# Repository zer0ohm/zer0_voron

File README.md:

# zer0_voron
## About zer0_voron
A repository for compiling modified parts, or a [hashtag](https://twitter.com/search?q=%23zer0_voron) to be added to tweets about VORON.

## BOM
Under development: It is a modification of an existing component, but it has never been tested and is "very" experimental. (To be tested soon, but undecided.)
### Shoiko(背負子)
 * Rear mounting of electrical components mod for VORON2.4
 * din_rail_mount_a/b inspired from [SnakeOil-XY](https://github.com/SnakeOilXY/SnakeOil-XY/blob/master/BETA2_Release/STLs/Panels/Back-panel/Bottom/4x_din-holder.stl)
 
| Part | Qty | Sourcing | Description/Note |
|---------|-------|----------------| ------------------ |
| din_rail_mount_x2 | 2 | Print part([STEP](./CAD/din_rail_mount_x2.step) or [STL](./STLs/din_rail_mount_x2.stl)) |  |
| SHCS M3x** | 2 | Local store | Length are TBD. |
| M3 Roll-in T-Nut | 2 | [AliExpress](https://www.aliexpress.com/item/32805163712.html) |  |
| SB2040 Cable-harness <br> or <br> 2-wire 18AWG Robot Cable(3 meter) + 2-wire AWG22 Robot Cable(3 meter) | 1 | [AliExpress](https://www.aliexpress.com/item/1005004819126687.html) <br> or <br> [Misumi(AWG18)](https://jp.misumi-ec.com/vona2/detail/222000262826/?HissuCode=%EF%BE%9B%EF%BE%8E%EF%BE%9E%EF%BE%84%EF%BD%AF%EF%BE%8C%EF%BE%9FDPC3+AWG18X2C-3) + <br> [Misumi(AWG22)](https://jp.misumi-ec.com/vona2/detail/222000262826/?HissuCode=%EF%BE%9B%EF%BE%8E%EF%BE%9E%EF%BE%84%EF%BD%AF%EF%BE%8C%EF%BE%9FDPC3+AWG22X2C-3)| Length are TBD. See [Cable Processing](./Docs/cable_processing.md) |
| RJ11 Cable | 1 | [Misumi](https://jp.misumi-ec.com/vona2/detail/110500076440/?HissuCode=CBLRJ050-666-S-07-SV) | For BTT Octopus only. See [Cable Processing](./Docs/cable_processing.md) |
| Toolhead PCB | 1 | [AliExpress](https://www.aliexpress.com/item/1005004675264551.html) | AliExpress's link is example for in Stealthburner. |
| BHCS M5x10 | 2 | Stock or Local store | Replace of screws due to removal of "XY Cable Chain Bridge". |

### Modified Corner Brackets
 * Attempt to determine if printed brackets can be used to strengthen rigidity
 * model based Misumi's HBLFSN5(2mm narrower to avoid interference with Z_Idler)

| Part | Qty | Sourcing | Description/Note |
|---------|-------|----------------| ------------------ |
| 2020Frame Corner Bracket 18mmWide | 12 | Print part([STEP](./CAD/2020_CornerBracket_18mm_x12.step) or [STL](./STLs/2020_CornerBracket_18mm_x12.stl)) ||
| SHCS M5x10 | 24 | Local store |  |
| M5 Roll-in T-Nut | 24 | [AliExpress](https://www.aliexpress.com/item/32805163712.html) |  |
| z_belt_cover_a_x2 | 2 | Print part([STEP](./CAD/z_belt_cover_a_x2_mod.step) or [STL](./STLs/z_belt_cover_a_x2_mod.stl)) | Use existing screws and nuts for mounting. |
| z_belt_cover_b_x2 | 2 | Print part([STEP](./CAD/z_belt_cover_b_x2_mod.step) or [STL](./STLs/z_belt_cover_b_x2_mod.stl)) | Use existing screws and nuts for mounting. |

### XYEndstop PCB for X_Carriage
 * Endstop PCB utilizing the switch mounting holes on the back side of X_Carriage 

| Part | Qty | Sourcing | Description/Note |
|---------|-------|----------------| ------------------ |
| Endstop PCB | 1 | order PCB yourself([KiCad](./KiCad/V2-X_carriage_XYEndSW)) or [Single item PCB from me](https://zer0ohm.booth.pm/) ||
| Self-tapping screw M2x12 or M2x14 | 2 | Local store or [AliExpress](https://www.aliexpress.com/item/1005002306042593.html) | PCB mount screw |
| D2F-L3-A1 microswitch | 1 | Digikey or Mouser or Local store | X Endstop |
| D2F-L3 microswitch | 1 | Digikey or Mouser or Local store | Y Endstop |
| JST-XH S3B-XH-A | 1 | Digikey or Mouser or Local store |  |
| JST XH XHP-3 | 1 | Digikey or Mouser or Local store | Qty is the number used on this PCB only, the number may vary depending on the connection point. |

### Front Skirt PowerUI Mod(for 350mm build only)
 * Mod to bring "inlet and switch"(PowerUI) to front skirt
 * Can divert parts used in existing front_skirt_a and power_inlet_filtered

| Part | Qty | Sourcing | Description/Note |
|---------|-------|----------------| ------------------ |
| front_skirt_a_mod | 1 | Print part([STEP](./CAD/front_skirt_a_mod.step) or [STL](./STLs/front_skirt_a_mod.stl)) ||
| [Optional] power_inlet_filtered_mod | 1 | Print part([STEP](./CAD/power_inlet_filtered_mod.step) or [STL](./STLs/power_inlet_filtered_mod.stl)) | Optional part. May use original parts. |

## Klipper_Configs
* Config for BTT Octopus+Mellow SB2040
* based [VORON's config](https://github.com/VoronDesign/Voron-2/blob/Voron2.4/firmware/klipper_configurations/Octopus/Voron2_Octopus_Config.cfg) and [Mellow/KlipperCN's config](https://mellow.klipper.cn/#/board/fly_sb2040/cfg)

| File | Description/Note |
|------|------------------|
| printer.cfg | |
| steppers.cfg | XYZ motor drive settings |
| toolhead.cfg | SB2040 settings |
| octopus_heatmanage.cfg | Bed-heater and FAN(excl toolhead fans) control |
| neopixel.cfg | lighting settings in chamber |
| macros.cfg | |
| display.cfg | BTT Mini12864 settings |

## What is Shoiko?
Shoiko(背負子)  is an Japanese word meaning "backpack". (naming inspired from [Kirigami](https://github.com/christophmuellerorg/voron_0_kirigami_bed).)

## License
This design are partially derived from the existing Voron parts and hence follow the same License, [GNU GPLv3](https://www.gnu.org/licenses/gpl-3.0.html).

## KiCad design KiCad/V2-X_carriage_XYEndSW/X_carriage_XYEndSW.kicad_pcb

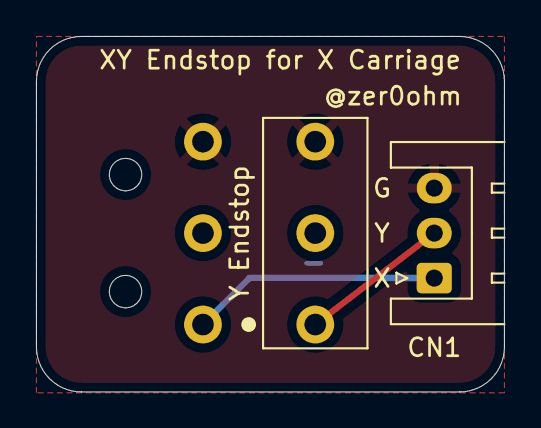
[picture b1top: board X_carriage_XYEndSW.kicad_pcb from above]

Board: 2 copper layers, 26.0 x 19.8 mm, 3 parts (1 on the bottom side), 3 nets.

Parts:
CN1: S3B-XH-A; JST_XH_S3B-XH-A_1x03_P2.50mm_Horizontal
SW1: D2F-L3-A1; D2F-x_A1
SW2: D2F-L3; D2F-x_T

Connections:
/X_sw: CN1.1, SW1.1 (A)
/Y_sw: CN1.2, SW2.1 (B)
GND: CN1.3, SW1.3 (B), SW2.3 (A)

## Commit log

2022-09-29 Add alpha version BOM
2022-09-29 fix qty num
2022-10-02 Update README.md
    fix BOM
2022-11-30 add design/config files
2022-11-30 fix links
2022-11-30 fix z_belt_cover filenames
